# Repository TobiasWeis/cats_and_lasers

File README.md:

# cats_and_lasers
Code and schematics for the laserturret cat-toy as described at [my blog](http://www.tobias-weis.de/cats-and-lasers/) 

## Final device

## Hardware used
* AZDelivery NodeMCU Lua Amica Modul V2
* DAGU pan/tilt servo kit https://robosavvy.com/store/dagu-pan-tilt-kit-with-servos.html
* Some male and female pinheaders
* A blank 7cmx10cm PCB that I milled in a CNC

## Software used
* Arduino IDE and several ESP2866-libraries to compile for the NodeMCU
* HTML/Javascript/JQuery/Bootstrap to create the website-frontend
* Eagle to design the schematic and the (pcb) board-layout
* Chillipeppr/Jpadie workspace to create G-Code for the mill
* Python/jupyter to simulate the servo-movements

## Calculating the servo-sweeps
I created the jupyter-notebook ServoSweepCalculator.ipynb located in the other_scripts folder

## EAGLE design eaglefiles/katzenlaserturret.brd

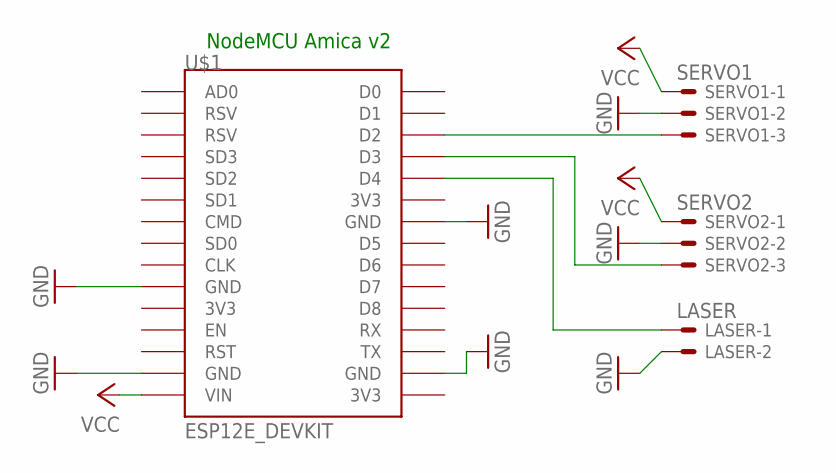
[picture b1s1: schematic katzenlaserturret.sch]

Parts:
LASER: LASER; 22-23-2021
SERVO1: SERVO1; 22-23-2031
SERVO2: SERVO2; 22-23-2031
U$1: ESP12E_DEVKIT

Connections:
GND: LASER.2, SERVO1.2, SERVO2.2, U$1.GND@0 (GND), U$1.GND@1 (GND), U$1.GND@2 (GND), U$1.GND@3 (GND)
unnamed: SERVO1.3, U$1.D2
unnamed: SERVO2.3, U$1.D3
unnamed: LASER.1, U$1.D4
VCC: SERVO1.1, SERVO2.1, U$1.VIN

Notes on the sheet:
NodeMCU Amica v2

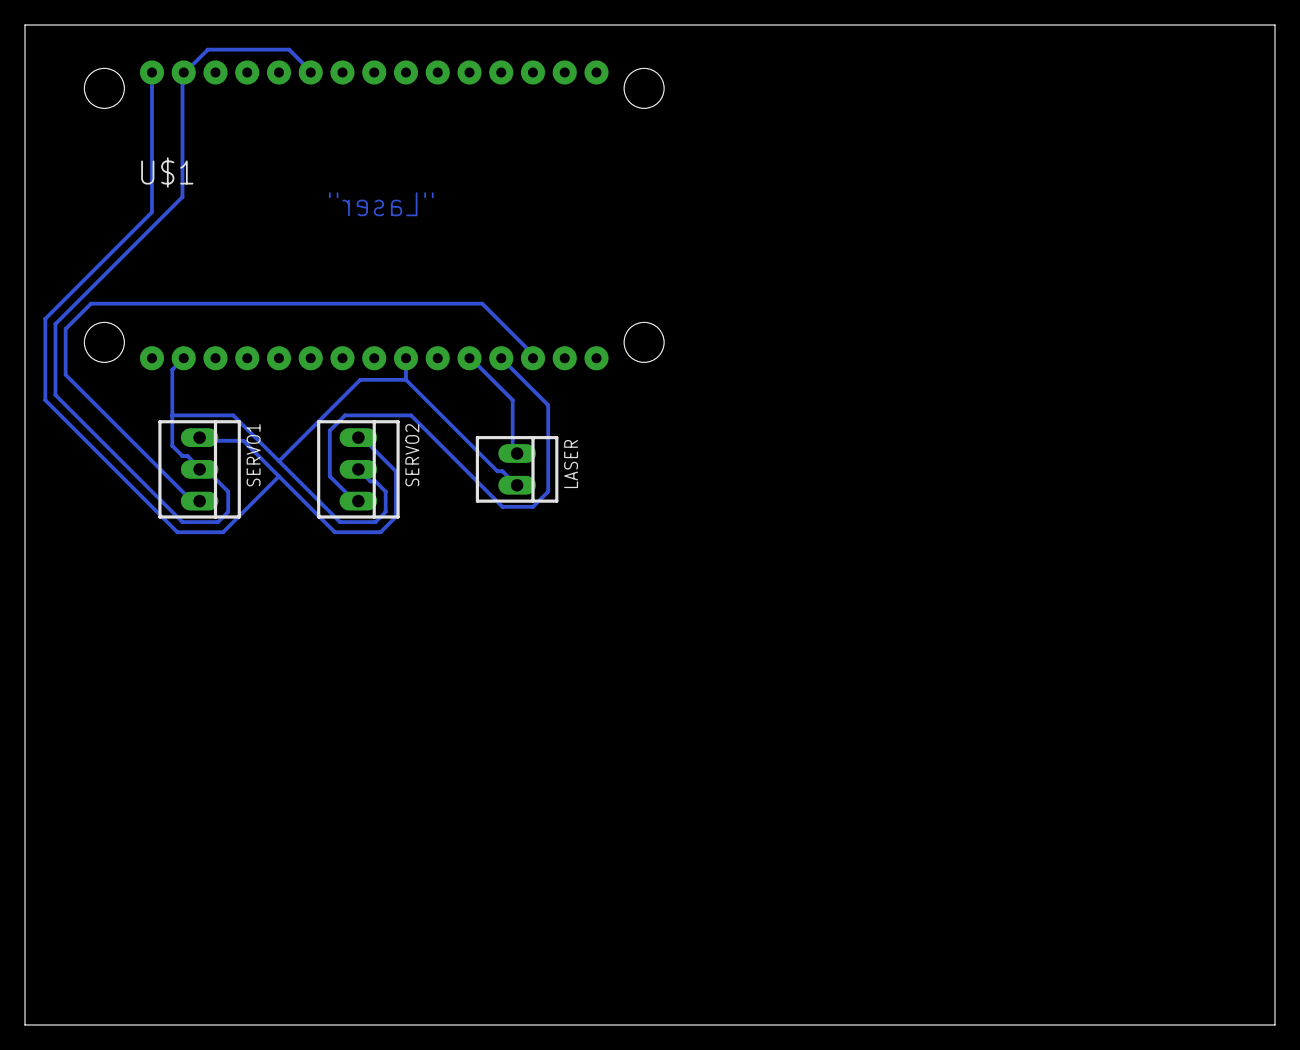
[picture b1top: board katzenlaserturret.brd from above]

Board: 2 copper layers, 100.0 x 80.0 mm, 4 parts (0 on the bottom side), 5 nets.

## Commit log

2019-10-12 added code
2019-10-12 added eaglefiles
2019-10-12 added image and more on README
2019-10-12 added image
2019-10-12 more on README
2019-10-12 added servosweep calculator script and description
